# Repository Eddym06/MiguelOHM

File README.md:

# MiguelOHM

Proyecto de la materia de **Microcontroladores**: un carrito controlado a distancia, con su propio
control remoto, navegación autónoma por GPS y una página web de control desde el celular.

```
 Control remoto ──433 MHz──► ESP32-P4 ══SPI══ ESP32-S3 ──WiFi──► Celular (página web)
 (ESP32-S3 + OLED)           (cerebro del carrito)  (puerta de enlace)
```

## Qué hace

- **Control remoto** con dos joysticks, modo giroscopio, freno motor, control de luces y un OLED con
  6 pantallas (velocímetro, RPM, inclinación, estado del enlace…).
- **Carrito** con dos motores con encoder (PID de velocidad, giro por motor + servo), faros, LEDs RGB en
  las ruedas, tira LED trasera estilo F1, GPS, LIDAR, IMU y medición de batería.
- **Página web** servida por el propio carrito: control táctil, mapa con brújula, ajustes, pruebas de
  componentes y modo autónomo (el carrito va a un punto marcado en el mapa esquivando obstáculos).
- El enlace 433 MHz y el WiFi **nunca están activos a la vez**: el primero en conectarse apaga al otro.

## Estructura

| Carpeta | Contenido |
|---|---|
| [Placa_Control_Remoto/](Placa_Control_Remoto/) | PCB del control (KiCad: `KAKATA_RC433_V1`) y su firmware en [Codigo/](Placa_Control_Remoto/Codigo/README.md) (PlatformIO, Arduino, ESP32-S3). |
| [Codigo Carrito/](Codigo%20Carrito/README.md) | Firmware del carrito en ESP-IDF: `p4/` (cerebro), `s3/` (WiFi + web), `shared/` (protocolos) y `tests/`. |
| [Diseño Caja 3D/](Diseño%20Caja%203D/) | Cajas para impresión 3D (FreeCAD). |
| [Placa_Carrito/](Placa_Carrito/) | PCB del carrito (KiCad): [Tesla/](Placa_Carrito/Tesla/README.md) con un solo ESP32-S3 y expansor PCA9555, y la placa modular S3+P4. |
| [Documentación/](Documentación/) | Documento del proyecto y registro de cambios. |

## Empezar

- **Control remoto:** abrir `Placa_Control_Remoto/Codigo` con PlatformIO y `pio run -t upload`.
- **Carrito:** necesita ESP-IDF 5.5 (P4) y 5.3 o superior (S3). Instrucciones, tabla de pines pendientes y
  lista de lo que falta validar en [Codigo Carrito/README.md](Codigo%20Carrito/README.md).
- **Pruebas de la lógica del carrito en la PC:** `bash "Codigo Carrito/tests/run_host_tests.sh"`.

## Estado

| Parte | Estado |
|---|---|
| Firmware del control remoto | Compila. Pendiente de probar en la PCB. |
| Firmware del carrito (P4 y S3) | Compila; lógica pura probada en la PC (97 verificaciones). Pines pendientes de la PCB del carrito. |
| Página web | Revisada en navegador con datos simulados. Pendiente de probar con el carrito real. |

Antes de las pruebas con hardware, revisar la sección «Sin validar en hardware» del README del carrito
(sentido de ejes y motores, encoders, PID, protocolo del LIDAR y del GPS).

## Simulación

[Modelos y resultados por placa](Simulación/README.md).

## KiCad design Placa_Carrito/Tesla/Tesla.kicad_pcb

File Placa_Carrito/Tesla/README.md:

# Placa Tesla (carrito): guía del diseño

PCB del carrito con **un solo ESP32-S3** (módulo WROOM-1 N16R2) y un expansor de pines **PCA9555**. Este documento explica cómo está organizado el esquemático, qué cambió respecto a las versiones anteriores y, sobre todo, **qué implica para el código** (para Eddy).

Archivos relacionados:

| Archivo | Contenido |
|---|---|
| [ASIGNACION_PINES.md](ASIGNACION_PINES.md) | Qué va en cada GPIO del S3, en cada pin del PCA9555 y en el conector J20. |
| [CAMBIOS.md](CAMBIOS.md) | Registro detallado de los cambios de esta revisión (qué, por qué y cómo verificarlo). |
| [Tesla_BOM.csv](Tesla_BOM.csv) | Lista de materiales. |
| `Tesla.kicad_pro` | Proyecto de KiCad 10 (abrirlo desde aquí). |

## Estructura del esquemático

La hoja raíz (`Tesla.kicad_sch`) tiene dos cosas: los **conectores externos**, cada uno en su cuadro y unido con cable directo (sin etiquetas) a los pines de la hoja `Externo`, y la hoja `USB-C`. Todo lo demás vive dentro de `Externo`, donde las hojas se unen por etiquetas. Los pines de `Externo` se llaman como la señal (`SERVO_1`, `ENC_A1`, `NRF_CE`...) y por dentro se unen a la red `GPIOn` o `EXP_GPIOn` del bloque de control.

**En la raíz (lo que el usuario toca):**

| Cuadro | Conectores |
|---|---|
| Batería | J6 (borne WAGO 2604-1102, 12 V) |
| Motores | J4 y J5, un conector PH2.0 de 6 pines por motor JGB37-520 (motor y encoder juntos) |
| GPS e IMU | J10 (GPS M100 Pro) y J15 (GY-521) |
| Servos | J7 (dirección), J8 y J9 |
| LiDAR | J11 y R24 (pull-down de la señal de control) |
| Tira LED | J16 (WS2812) |
| Radio nRF24L01+ | U2 (módulo nRF24L01 con conector, fuera de la placa principal) |
| Luces | J21 y J24 (faros, uno por LED), J22 y J23 (intermitentes izquierdo y derecho): un conector PH2.0 de 2 pines por canal para los LED de 1 W |
| Expansión | J20 (socket hembra 1x16) |
| USB-C | hoja `usb.kicad_sch`: J3, protección ESD U13 y R61 y R62 (CC) |

**Dentro de `Externo`:**

| Hoja | Archivo | Contenido |
|---|---|---|
| Alimentacion | `alimentacion.kicad_sch` | Contenedor de: protección de batería (`alim_proteccion`), medición (`alim_medicion`) y dos bucks (`alim_buck_3v3` y `alim_buck_5v`; el de 5 V incluye el filtro del LiDAR). |
| Control ESP32 | `control.kicad_sch` | **Solo** el ESP32-S3 con su circuito mínimo (reset, BOOT, filtrado de 3V3) y el PCA9555 con su filtrado. Incluye los pull-ups que exige el PCA9555 en SCL, SDA e INT (4,7 kΩ, 4,7 kΩ y 10 kΩ). Los pull-downs de las salidas no van aquí: viven junto a la carga que protegen. |
| Drivers motores | `motores.kicad_sch` | DRV8424 y pull-downs de arranque de APH, BPH y nSleep. |
| Faros | `faros.kicad_sch` | Drivers del alumbrado (faros e intermitentes, AL8860; los LED van afuera) y adaptador 3,3 V a 5 V para la tira WS2812B (J16). |

Reglas de dibujo aplicadas a todas las hojas:

- En la raíz, cada señal va con cable directo del pin de `Externo` al pin del conector. Entre ICs y hojas internas se usan etiquetas (jerárquicas en el borde de cada hoja, globales entre pines internos, locales dentro de una hoja). Los cables solo unen un pasivo con su pin.
- Cada pasivo se conecta con cable corto, componente, cable corto y símbolo de alimentación. Nada se conecta directo a un nodo.
- Las flechas de 3V3, 5V y VM apuntan hacia arriba o de lado, nunca hacia abajo, y muestran su nombre.
- Los valores de componentes verticales van girados 90° junto al cuerpo.
- Cada grupo funcional va dentro de un marco punteado con título.
- Un solo GND en todo el proyecto.
- Las librerías oficiales de Espressif no se modifican.

### Conector de los motores (JGB37-520, J4 y J5)

Orden de pines del cable de 6 hilos con PH2.0 (de las imágenes del vendedor; comprobar con el motor):

| Pin | Señal | Cable |
|---|---|---|
| 1 | M1, motor + | rojo |
| 2 | GND del encoder | negro |
| 3 | C1, fase A | amarillo |
| 4 | C2, fase B | verde |
| 5 | VCC del encoder (3V3) | azul |
| 6 | M2, motor - | blanco |

Intercambiar M1 y M2 invierte el giro. El encoder (11 PPR, 3,3 a 5 V) se alimenta a 3,3 V; nunca conectar los 12 V del motor al VCC del encoder.

## Qué cambió y por qué importa al firmware

1. **Un solo microcontrolador.** El P4 salió de esta placa (vive en `../Placa_Modular_S3_P4`). Control, WiFi y web corren en el S3. El firmware actual de `Codigo Carrito/` está pensado para P4 más S3; hay que portarlo a un único S3 (tabla de pines en [ASIGNACION_PINES.md](ASIGNACION_PINES.md)).
2. **Pines de arranque sin uso.** GPIO3, GPIO45 y GPIO46 quedan sin conectar. GPIO0 es solo el botón BOOT: no se puede usar como entrada o salida del programa.
3. **Los nombres de los pines del bloque de control son GPIO.** En el firmware sigue habiendo nombres funcionales (`PIN_ENC_L_A`, etc.); la equivalencia con el GPIO está en la tabla de `ASIGNACION_PINES.md`.
4. **Expansor PCA9555.** Las señales lentas (CE e IRQ del nRF24, dirección y sleep de los motores, fallo del driver, LEDs de estado) ya no son pines del S3: se leen y escriben por I2C (ver siguiente sección).
5. **Bus I2C compartido** (GPIO39 SCL, GPIO40 SDA, pull-ups de 4,7 kΩ): GPS, IMU, INA219 y PCA9555 (0x20). **GPIO39, GPIO40 y GPIO42 (INT) no son pines libres** y no salen de la hoja de control. Por eso el GPS, la IMU, el INA219 y los pines I2C de J20 **no tienen bus I2C hacia el S3 todavía** (decisión pendiente: ver Pendiente).
6. **Radio nRF24** por SPI en GPIO10 (CSN), GPIO11 (MOSI), GPIO12 (SCK), GPIO13 (MISO). CE e IRQ van por el expansor.
7. **USB-C del S3** (hoja `USB-C`) para programar, JTAG y consola (GPIO19 D-, GPIO20 D+). UART0 (GPIO43 TX, GPIO44 RX) va a un segundo USB-C (J2, hoja `USB-UART`) con puente CH340C y auto-reset por DTR y RTS (EN y GPIO0).
8. **Motores y encoders** salen por un solo conector de 6 pines por motor (J4 y J5), con el encoder a 3,3 V.

## Programar el expansor PCA9555

Los 16 pines `EXP_GPIO0` a `EXP_GPIO15` no son GPIO del S3: son dos puertos de 8 bits que se controlan por I2C con el chip en la dirección **0x20** (A0, A1 y A2 a GND). Un bit del puerto 0 es `EXP_GPIO0` a `7`; uno del puerto 1 es `EXP_GPIO8` a `15`.

Registros (el primer byte de cada transferencia elige el registro):

| Reg | Función |
|---|---|
| 0x00 / 0x01 | Leer puerto 0 / puerto 1 (entradas) |
| 0x02 / 0x03 | Escribir salidas del puerto 0 / 1 |
| 0x04 / 0x05 | Invertir polaridad (se deja en 0) |
| 0x06 / 0x07 | Configuración del puerto 0 / 1: **1 = entrada, 0 = salida** |

Al encender, todos los pines son entradas con un pull-up interno de unos 100 kΩ. Por eso APH, BPH, nSleep y CE tienen pull-down de 10 kΩ: el driver arranca dormido y el nRF24 con CE en bajo.

Uso de cada pin en esta placa:

| Pin | Señal | Dirección |
|---|---|---|
| `EXP_GPIO0` | NRF_CE | salida |
| `EXP_GPIO1` | NRF_IRQ | entrada |
| `EXP_GPIO2`, `3`, `4` | APH, BPH, nSleep del DRV8424 | salida |
| `EXP_GPIO5` | nFAULT del DRV8424 | entrada |
| `EXP_GPIO6`, `7` | LED_AP, LED_AN | salida, **activos en bajo** |
| `EXP_GPIO8`, `9` | LED_BP, LED_BN | salida, **activos en bajo** |
| `EXP_GPIO10` a `15` | libres, salen por J20 | a elección |

Valores iniciales recomendados (se escriben antes de configurar la dirección, para que no haya pulsos): puerto 0 salidas en `0xC0` y puerto 1 en `0x03` (todo en bajo salvo los LEDs, que en alto quedan apagados). Configuración: puerto 0 en `0x22` y puerto 1 en `0xFC`.

Ejemplo con ESP-IDF 5.x (sin compilar; sirve de guía):

```c
#include "driver/i2c_master.h"

static i2c_master_dev_handle_t pca;

static void pca_write(uint8_t reg, uint8_t val) {
    uint8_t b[2] = { reg, val };
    i2c_master_transmit(pca, b, 2, 100);
}
static uint8_t pca_read(uint8_t reg) {
    uint8_t v = 0;
    i2c_master_transmit_receive(pca, &reg, 1, &v, 1, 100);
    return v;
}

void pca_init(void) {
    i2c_master_bus_handle_t bus;
    i2c_master_bus_config_t bc = {
        .i2c_port = I2C_NUM_0, .sda_io_num = GPIO_NUM_40, .scl_io_num = GPIO_NUM_39,
        .clk_source = I2C_CLK_SRC_DEFAULT, .glitch_ignore_cnt = 7,
    };
    i2c_new_master_bus(&bc, &bus);
    i2c_device_config_t dc = { .dev_addr_length = I2C_ADDR_BIT_LEN_7,
                               .device_address = 0x20, .scl_speed_hz = 400000 };
    i2c_master_bus_add_device(bus, &dc, &pca);

    pca_write(0x02, 0xC0);   // CE/APH/BPH/nSleep en 0, LEDs apagados
    pca_write(0x03, 0x03);   // LEDs del puerto 1 apagados
    pca_write(0x06, 0x22);   // puerto 0: bits 1 (IRQ) y 5 (nFAULT) son entradas
    pca_write(0x07, 0xFC);   // puerto 1: solo los bits 0 y 1 son salidas
}
```

Para cambiar un solo pin se guarda una copia del registro de salida en una variable y se modifica solo ese bit (por ejemplo `out0 |= 1 << 4; pca_write(0x02, out0);`). Para leer el fallo del driver: `pca_read(0x00) & (1 << 5)`.

Interrupción: `INT` va a **GPIO42** y baja cuando cambia alguna entrada. Se apaga al leer los registros 0x00 y 0x01. Configurar GPIO42 como entrada con flanco de bajada y leer los dos puertos en el manejador.

Límites: cada acceso tarda unos 100 µs a 400 kHz. Sirve para CE, dirección, sleep y LEDs; **no** para PWM ni señales rápidas (AEN y BEN, los PWM de los motores, están en pines nativos del S3).

## Verificación contra los datasheets

Se contrastó el diseño con el datasheet del ESP32-S3-WROOM-1 v1.8 y el del PCA9555 de TI. Detalle en [ASIGNACION_PINES.md](ASIGNACION_PINES.md#verificación-contra-los-datasheets). Correcciones hechas: C131 de 10 a 22 µF (filtrado de 3V3 del módulo) y R54 de 100 kΩ a 10 kΩ (pull-down de CE frente al pull-up interno del PCA9555).

## Pendiente

- En KiCad: **Actualizar PCB desde esquema** con la opción de actualizar huellas. Cambiaron J4 y J5 (ahora PH2.0 de 6 pines), J13 y J14 desaparecieron, J20 pasa a socket hembra y los nombres de red cambiaron con la hoja `Externo` y la hoja `USB-C`. Hasta entonces el DRC con paridad marca conflictos de red.
- Decidir cómo llega el I2C al GPS, la IMU y el INA219 (GPIO39 y GPIO40 están ocupados por el PCA9555 y no salen de Control).
- Rutear la PCB (hoy solo tiene las huellas colocadas) y revisar las reglas del DRC de U1 (anillos y taladros de las vías internas).
- Portar el firmware a un único S3 (`Codigo Carrito/`), con el driver del PCA9555 de arriba.
- Datasheets: carpeta `Datasheets/` en la raíz del repositorio (faltan algunos conectores, el GPS y el LiDAR; ver su README).

## Alimentación en la jerarquía (entradas y salidas de rieles)

- La hoja `Alimentacion` **saca** `VM`, `+3V3`, `+5V` y `GND` (bloque "Salidas de alimentacion"; el buck de 3V3, el de 5 V, la medición y la protección reciben `GND` y `VM` por pines).
- Cada hoja consumidora **recibe** solo los rieles que usa en su bloque "Entradas de alimentacion" (etiqueta jerárquica, un cablecito con giro y el símbolo de alimentación): Control (`+3V3`, `GND`), Drivers motores y Faros (`VM`, `GND`), Tira LED (`+5V`, `GND`), LEDs RGB (`+3V3`, `+5V`, `VM`, `GND`).
- En `Externo` cada pin de riel lleva una etiqueta global del mismo nombre, así todos los `GND`, `+3V3`, `+5V` y `VM` quedan unidos en toda la jerarquía. Sigue habiendo un solo `GND`.
- Los conectores de la raíz traen sus propios símbolos de alimentación (+5V, GND, +3V3...), que también son globales.

## Placa (PCB)

La placa ya tiene contorno de 130 x 170 mm, 4 capas, clases de red, zonas de cobre, zonas prohibidas de las antenas y todas las piezas colocadas (sin rutar). El detalle de la colocación, los cálculos, los cambios de piezas por existencias en JLCPCB y lo pendiente está en [PCB_NOTAS.md](PCB_NOTAS.md). La lista de piezas con códigos LCSC, existencias y precios está en `Tesla_BOM.csv` y `Tesla_BOM_JLCPCB.csv`. Se regenera con `herramientas/pcb_build.py`.

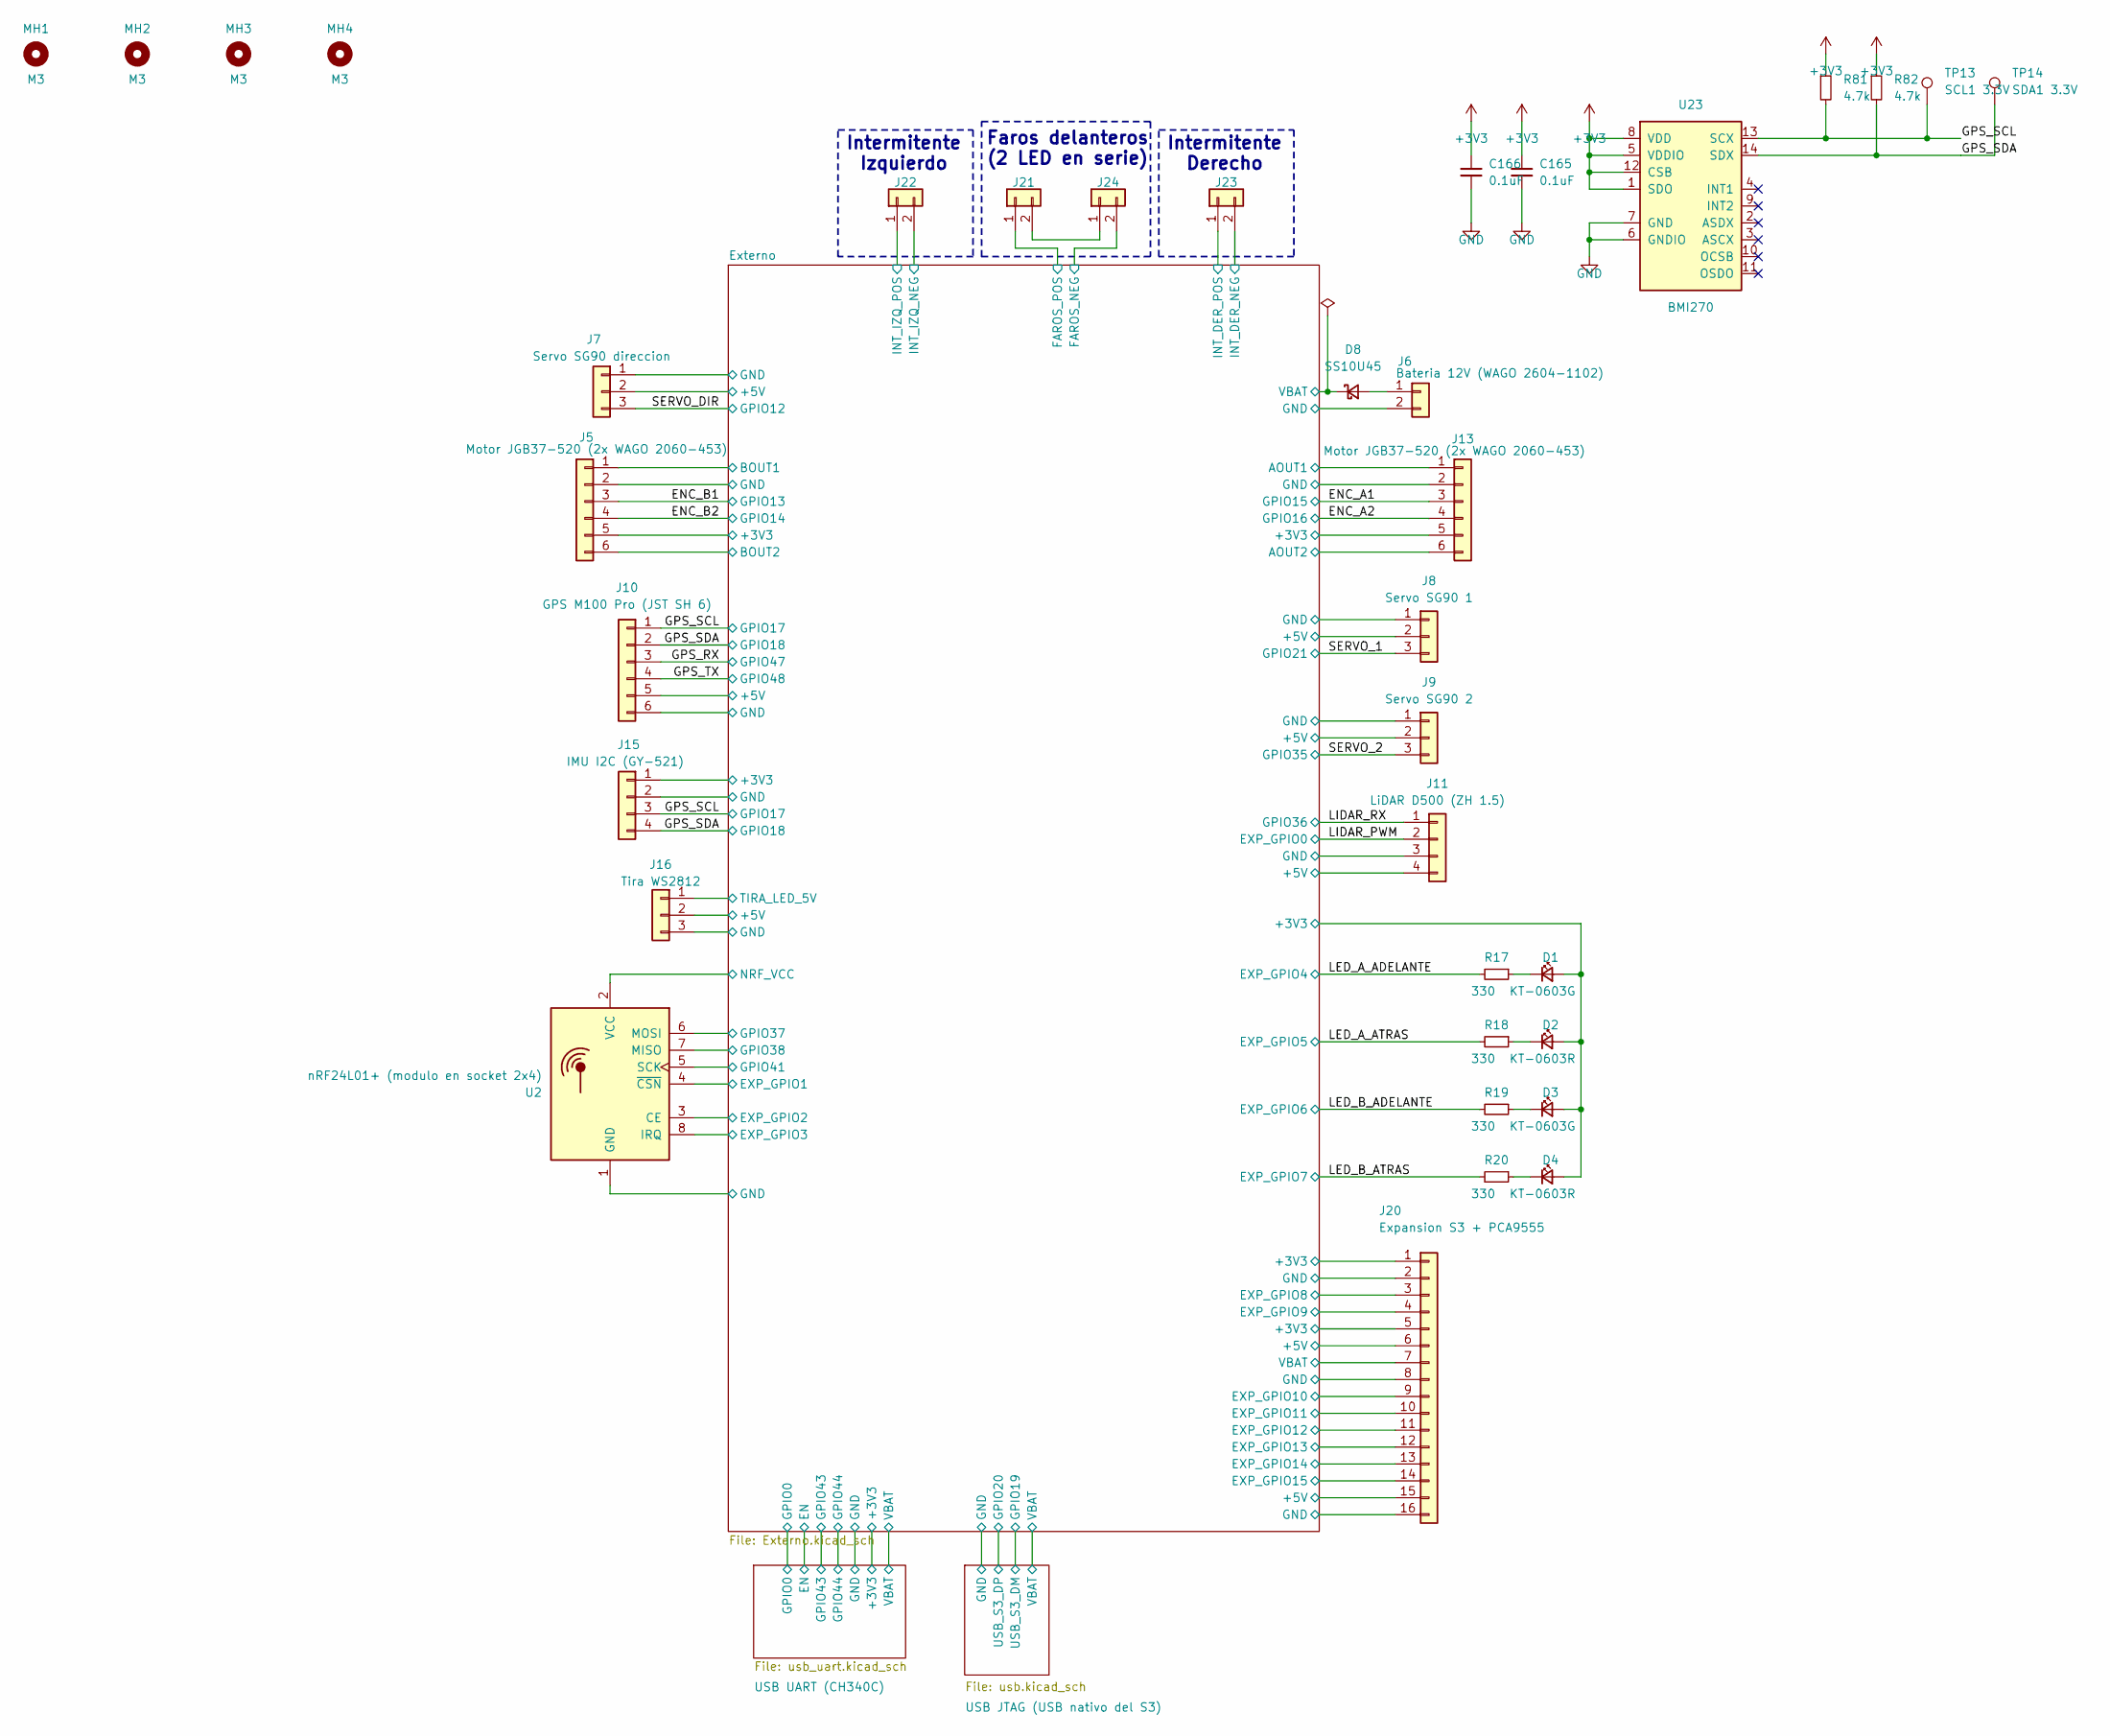
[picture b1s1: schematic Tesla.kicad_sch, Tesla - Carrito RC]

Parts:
C165, C166: 0.1uF; C_0402_1005Metric; LCSC C307331
D1, D3: KT-0603G; LED_0603_1608Metric; LCSC C12624
D2, D4: KT-0603R; LED_0603_1608Metric; LCSC C2286
D8: SS10U45; TO-277_SS10U45; LCSC C698773
J5, J13: Motor JGB37-520 (2x WAGO 2060-453); WAGO_2060-453_x2_6P_SMD; LCSC C2765056
J6: Bateria 12V (WAGO 2604-1102); WAGO_2604-1102_2P_THT; LCSC C3309286
J7: Servo SG90 direccion; PinHeader_1x03_P2.54mm_Horizontal; LCSC C492411
J8: Servo SG90 1; PinHeader_1x03_P2.54mm_Horizontal; LCSC C492411
J9: Servo SG90 2; PinHeader_1x03_P2.54mm_Horizontal; LCSC C492411
J10: GPS M100 Pro (JST SH 6); JST_SH_SM06B-SRSS-TB_1x06-1MP_P1.00mm_Horizontal; LCSC C160405
J11: LiDAR D500 (ZH 1.5); JST_ZH_B4B-ZR_1x04_P1.50mm_Vertical; LCSC C157997
J15: IMU I2C (GY-521); PinSocket_1x04_P2.54mm_Vertical; LCSC C2718488
J16: Tira WS2812; PinHeader_1x03_P2.54mm_Horizontal; LCSC C492411
J20: Expansion S3 + PCA9555; PinSocket_2x08_P2.54mm_Vertical; LCSC C30734
J21: Faro delantero 1; JST_PH_B2B-PH-K_1x02_P2.00mm_Vertical; LCSC C131337
J22: Intermitente izquierdo; JST_PH_B2B-PH-K_1x02_P2.00mm_Vertical; LCSC C131337
J23: Intermitente derecho; JST_PH_B2B-PH-K_1x02_P2.00mm_Vertical; LCSC C131337
J24: Faro delantero 2; JST_PH_B2B-PH-K_1x02_P2.00mm_Vertical; LCSC C131337
MH1, MH2, MH3, MH4: M3; MountingHole_3.2mm_M3
R17, R18, R19, R20: 330; R_0402_1005Metric; LCSC C25104
R81, R82: 4.7k; R_0402_1005Metric; LCSC C25900
TP13: SCL1 3.3V; TestPoint_Pad_D1.5mm
TP14: SDA1 3.3V; TestPoint_Pad_D1.5mm
U2: nRF24L01+ (modulo en socket 2x4); nRF24L01_Breakout; LCSC C239344
U23: BMI270; Bosch_LGA-14_3x2.5mm_P0.5mm; LCSC C2836813

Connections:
+3V3: C165.1, C166.1, D1.2 (A), D2.2 (A), D3.2 (A), D4.2 (A), J5.5, J13.5, J15.1, J20.1, J20.5, R81.1, R82.1, U2.2 (VCC), U23.1 (SDO), U23.5 (VDDIO), U23.8 (VDD), U23.12 (CSB); also elsewhere on the board
+5V: J7.2, J8.2, J9.2, J10.5, J11.4, J16.2, J20.6, J20.15; also elsewhere on the board
/ENC_A1: J13.3; also elsewhere on the board
/ENC_A2: J13.4; also elsewhere on the board
/ENC_B1: J5.3; also elsewhere on the board
/ENC_B2: J5.4; also elsewhere on the board
/Externo/AOUT1: J13.1; also elsewhere on the board
/Externo/AOUT2: J13.6; also elsewhere on the board
/Externo/BOUT1: J5.1; also elsewhere on the board
/Externo/BOUT2: J5.6; also elsewhere on the board
/Externo/EXP_GPIO1: U2.4 (~CSN); also elsewhere on the board
/Externo/EXP_GPIO2: U2.3 (CE); also elsewhere on the board
/Externo/EXP_GPIO3: U2.8 (IRQ); also elsewhere on the board
/Externo/EXP_GPIO8: J20.3; also elsewhere on the board
/Externo/EXP_GPIO9: J20.4; also elsewhere on the board
/Externo/EXP_GPIO10: J20.9; also elsewhere on the board
/Externo/EXP_GPIO11: J20.10; also elsewhere on the board
/Externo/EXP_GPIO12: J20.11; also elsewhere on the board
/Externo/EXP_GPIO13: J20.12; also elsewhere on the board
/Externo/EXP_GPIO14: J20.13; also elsewhere on the board
/Externo/EXP_GPIO15: J20.14; also elsewhere on the board
/Externo/FAROS_NEG: J24.2; also elsewhere on the board
/Externo/FAROS_POS: J21.1; also elsewhere on the board
/Externo/GPIO37: U2.6 (MOSI); also elsewhere on the board
/Externo/GPIO38: U2.7 (MISO); also elsewhere on the board
/Externo/GPIO41: U2.5 (SCK); also elsewhere on the board
/Externo/INT_DER_NEG: J23.2; also elsewhere on the board
/Externo/INT_DER_POS: J23.1; also elsewhere on the board
/Externo/INT_IZQ_NEG: J22.2; also elsewhere on the board
/Externo/INT_IZQ_POS: J22.1; also elsewhere on the board
/Externo/TIRA_LED_5V: J16.1; also elsewhere on the board
/Externo/VBAT: D8.1 (K), J20.7; also elsewhere on the board
/GPS_RX: J10.3; also elsewhere on the board
/GPS_SCL: J10.1, J15.3, R81.2, TP13.1, U23.13 (SCX); also elsewhere on the board
/GPS_SDA: J10.2, J15.4, R82.2, TP14.1, U23.14 (SDX); also elsewhere on the board
/GPS_TX: J10.4; also elsewhere on the board
/LED_A_ADELANTE: R17.2; also elsewhere on the board
/LED_A_ATRAS: R18.2; also elsewhere on the board
/LED_B_ADELANTE: R19.2; also elsewhere on the board
/LED_B_ATRAS: R20.2; also elsewhere on the board
/LIDAR_PWM: J11.2; also elsewhere on the board
/LIDAR_RX: J11.1; also elsewhere on the board
/SERVO_1: J8.3; also elsewhere on the board
/SERVO_2: J9.3; also elsewhere on the board
/SERVO_DIR: J7.3; also elsewhere on the board
GND: C165.2, C166.2, J5.2, J6.2, J7.1, J8.1, J9.1, J10.6, J11.3, J13.2, J15.2, J16.3, J20.2, J20.8, J20.16, U2.1 (GND), U23.6 (GNDIO), U23.7 (GND); also elsewhere on the board
unnamed: D1.1 (K), R17.1
unnamed: D2.1 (K), R18.1
unnamed: D3.1 (K), R19.1
unnamed: D4.1 (K), R20.1
unnamed: D8.2 (A), J6.1
unnamed: J21.2, J24.1

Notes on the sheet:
Intermitente Derecho
Faros delanteros (2 LED en serie)
Intermitente Izquierdo

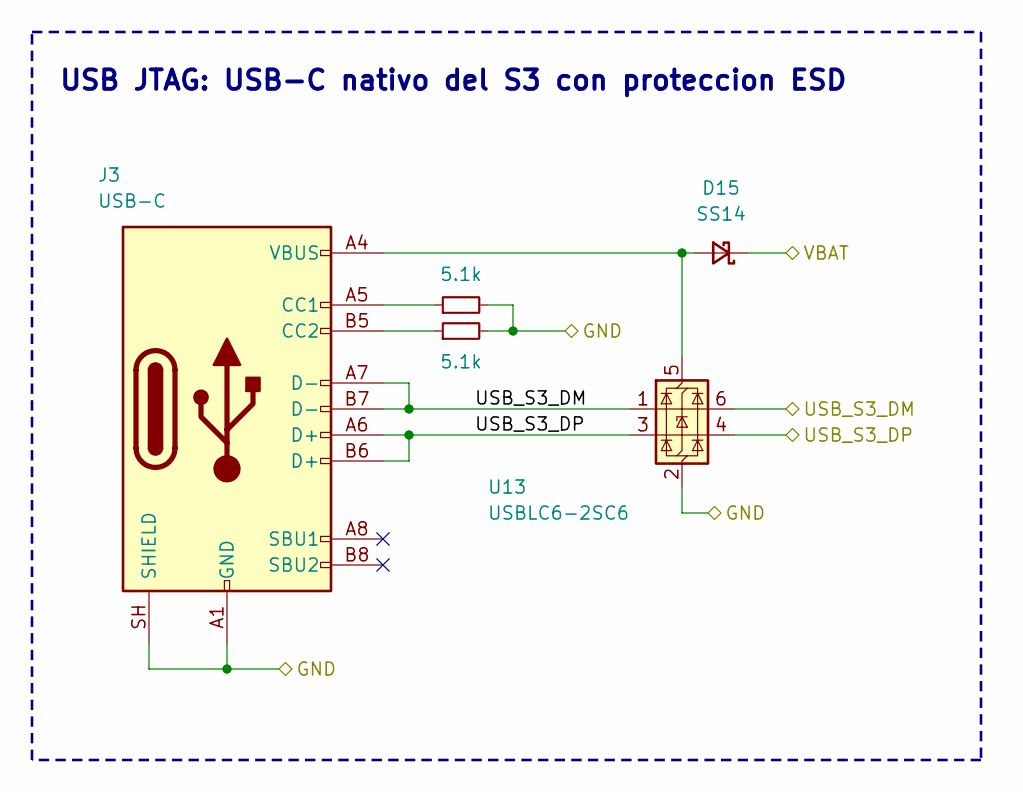
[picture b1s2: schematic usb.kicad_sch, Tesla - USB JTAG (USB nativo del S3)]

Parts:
D15: SS14; D_SMA; LCSC C2480
J3: USB-C; USB_C_Receptacle_HRO_TYPE-C-31-M-12; LCSC C165948
R61, R62: 5.1k; R_0402_1005Metric; LCSC C25905
U13: USBLC6-2SC6; SOT-23-6; LCSC C7519

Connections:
/Externo/VBAT: D15.1 (K); also elsewhere on the board
/USB JTAG (USB nativo del S3)/USB_S3_DM: J3.A7 (D-), J3.B7 (D-), U13.1 (I/O1), U13.6 (I/O1); also elsewhere on the board
/USB JTAG (USB nativo del S3)/USB_S3_DP: J3.A6 (D+), J3.B6 (D+), U13.3 (I/O2), U13.4 (I/O2); also elsewhere on the board
GND: J3.A1 (GND), J3.A12 (GND), J3.B1 (GND), J3.B12 (GND), J3.SH (SHIELD), R61.2, R62.2, U13.2 (GND); also elsewhere on the board
unnamed: D15.2 (A), J3.A4 (VBUS), J3.A9 (VBUS), J3.B4 (VBUS), J3.B9 (VBUS), U13.5 (VBUS)
unnamed: J3.A5 (CC1), R61.1
unnamed: J3.B5 (CC2), R62.1

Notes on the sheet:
USB JTAG: USB-C nativo del S3 con proteccion ESD

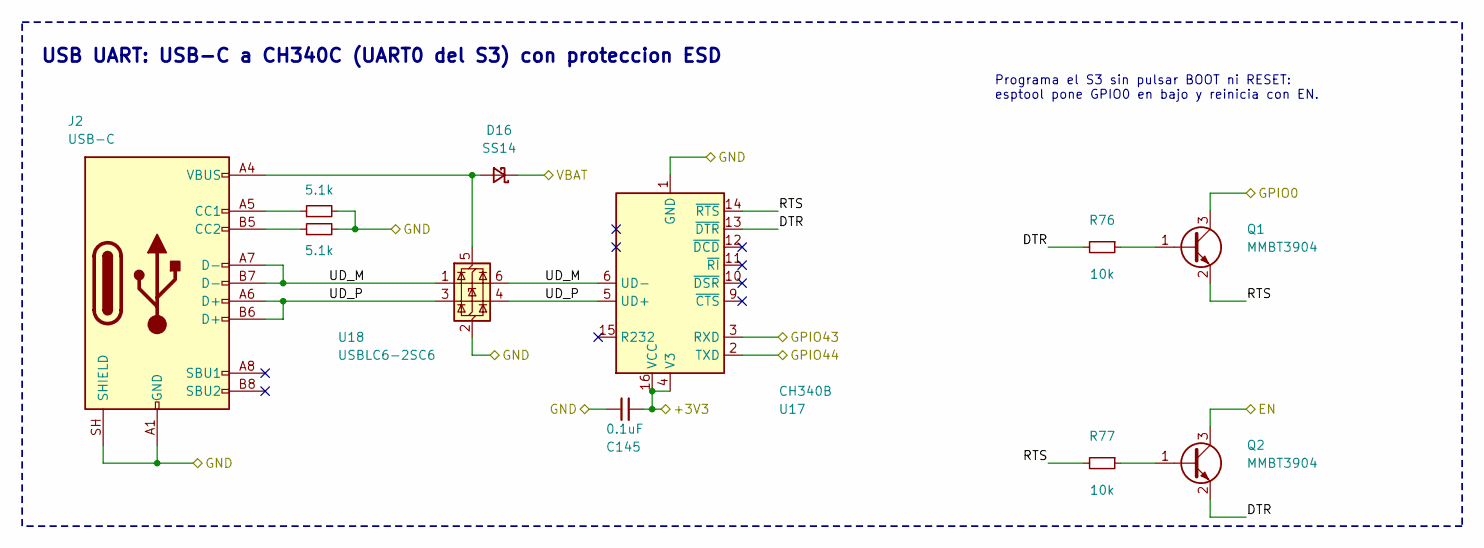
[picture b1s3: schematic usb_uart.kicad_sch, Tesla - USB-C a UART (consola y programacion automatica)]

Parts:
C145: 0.1uF; C_0402_1005Metric; LCSC C307331
D16: SS14; D_SMA; LCSC C2480
J2: USB-C; USB_C_Receptacle_HRO_TYPE-C-31-M-12; LCSC C165948
Q1, Q2: MMBT3904; SOT-23; LCSC C20526
R74, R75: 5.1k; R_0402_1005Metric; LCSC C25905
R76, R77: 10k; R_0402_1005Metric; LCSC C25744
U17: CH340B; SOIC-16_3.9x9.9mm_P1.27mm; LCSC C81010
U18: USBLC6-2SC6; SOT-23-6; LCSC C7519

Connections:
+3V3: C145.1, U17.4 (V3), U17.16 (VCC); also elsewhere on the board
/Externo/EN: Q2.3 (C); also elsewhere on the board
/Externo/GPIO0: Q1.3 (C); also elsewhere on the board
/Externo/GPIO43: U17.3 (RXD); also elsewhere on the board
/Externo/GPIO44: U17.2 (TXD); also elsewhere on the board
/Externo/VBAT: D16.1 (K); also elsewhere on the board
/USB UART (CH340C)/DTR: Q2.2 (E), R76.2, U17.13 (~DTR)
/USB UART (CH340C)/RTS: Q1.2 (E), R77.2, U17.14 (~RTS)
/USB UART (CH340C)/UD_M: J2.A7 (D-), J2.B7 (D-), U17.6 (UD-), U18.1 (I/O1), U18.6 (I/O1)
/USB UART (CH340C)/UD_P: J2.A6 (D+), J2.B6 (D+), U17.5 (UD+), U18.3 (I/O2), U18.4 (I/O2)
GND: C145.2, J2.A1 (GND), J2.A12 (GND), J2.B1 (GND), J2.B12 (GND), J2.SH (SHIELD), R74.2, R75.2, U17.1 (GND), U18.2 (GND); also elsewhere on the board
unnamed: D16.2 (A), J2.A4 (VBUS), J2.A9 (VBUS), J2.B4 (VBUS), J2.B9 (VBUS), U18.5 (VBUS)
unnamed: J2.A5 (CC1), R74.1
unnamed: J2.B5 (CC2), R75.1
unnamed: Q1.1 (B), R76.1
unnamed: Q2.1 (B), R77.1

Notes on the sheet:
USB UART: USB-C a CH340C (UART0 del S3) con proteccion ESD
Programa el S3 sin pulsar BOOT ni RESET: esptool pone GPIO0 en bajo y reinicia con EN.

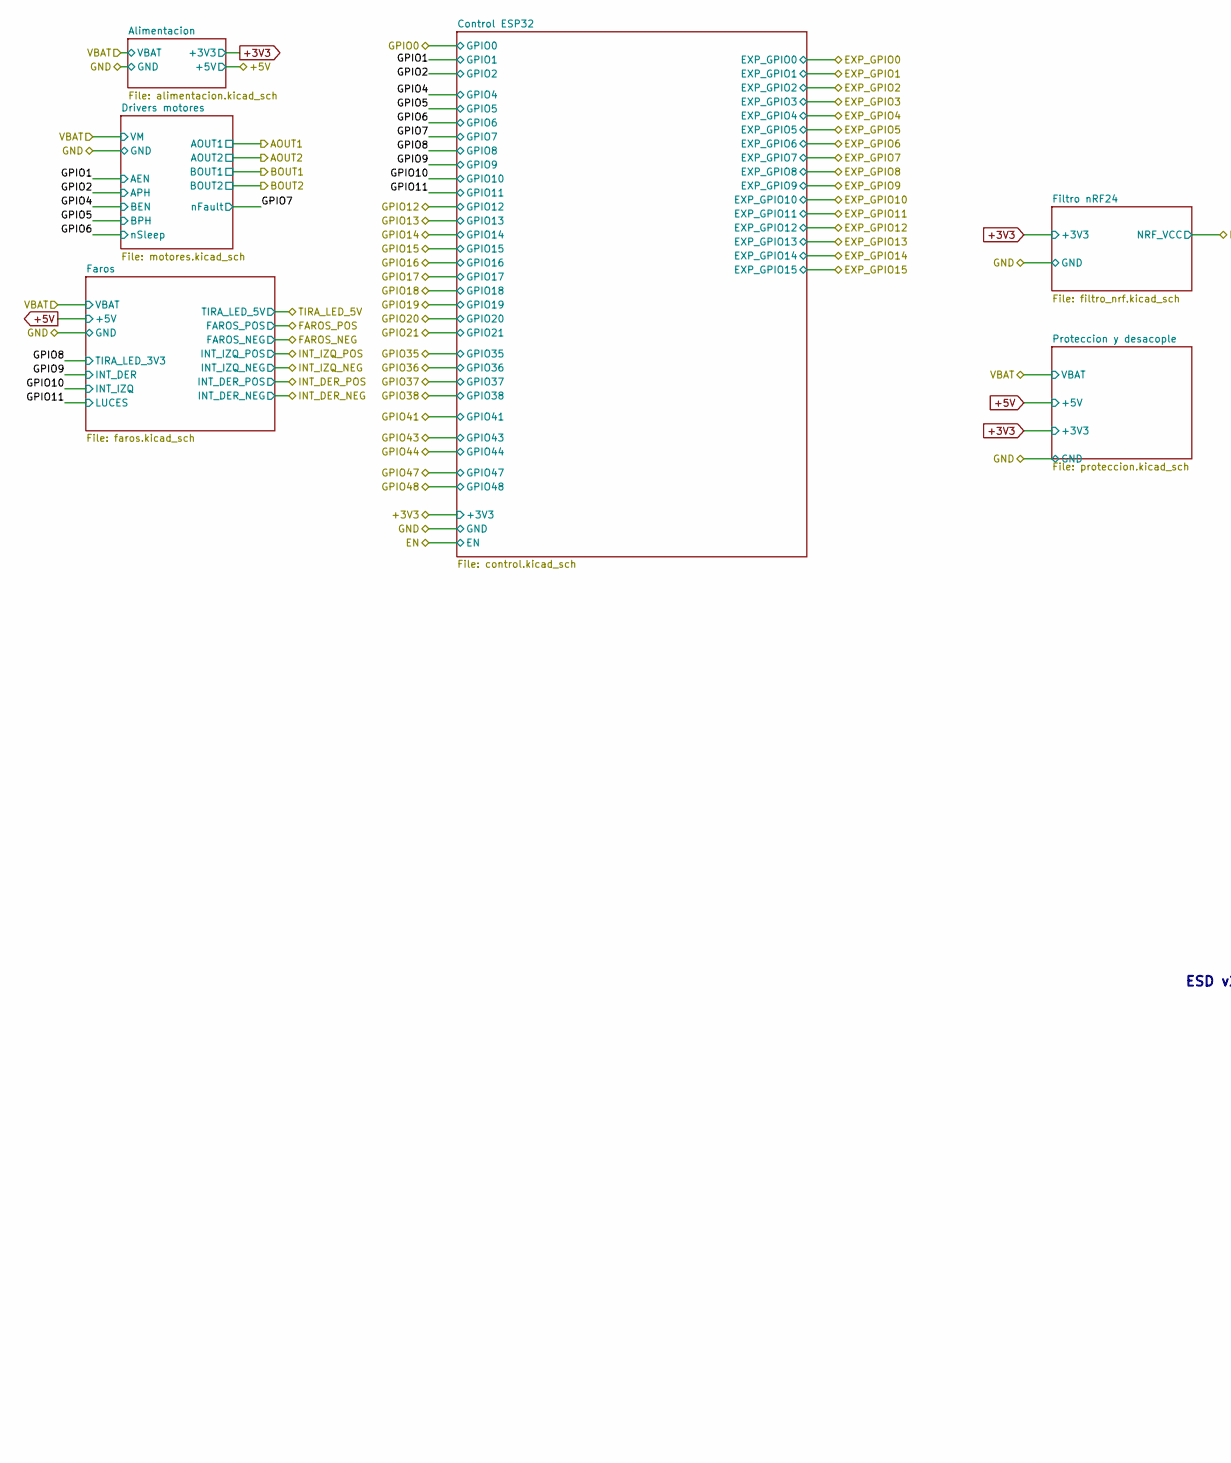
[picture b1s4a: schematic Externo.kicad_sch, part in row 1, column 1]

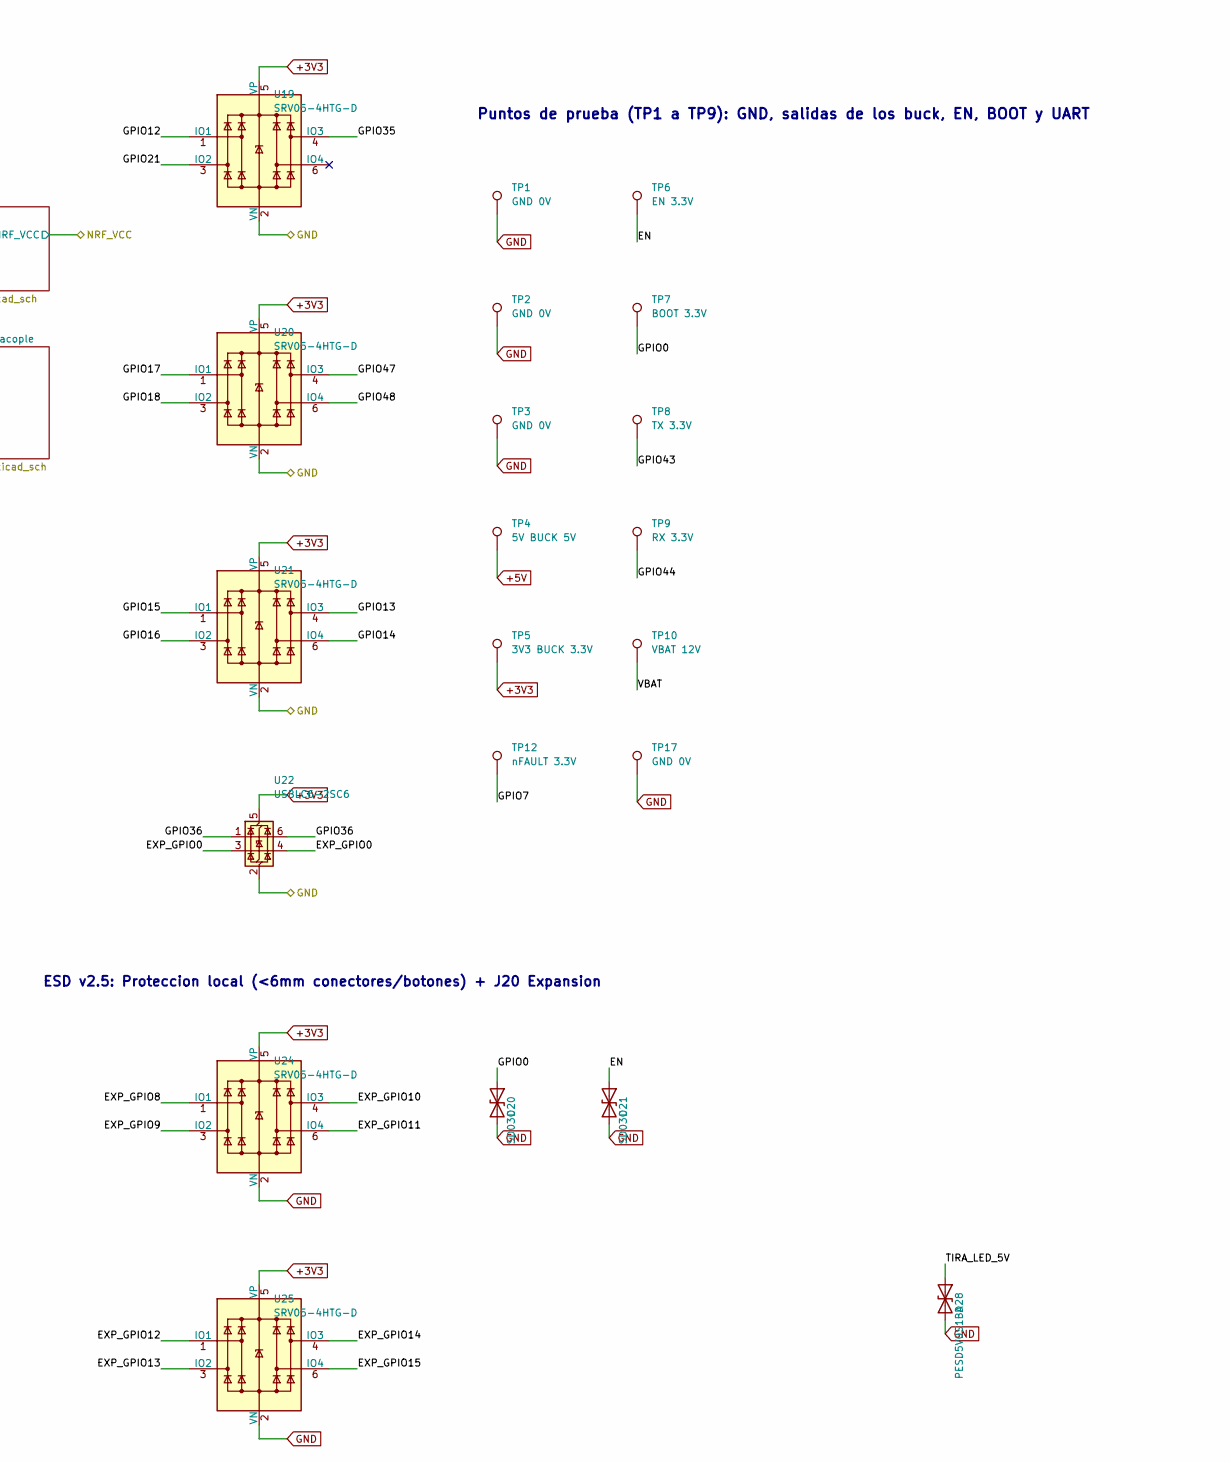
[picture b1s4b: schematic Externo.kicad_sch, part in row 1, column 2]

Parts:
D20, D21: SD03C; D_SOD-323; LCSC C502532
D28: PESD5V0S1BA; D_SOD-323; LCSC C2827694
TP1, TP2, TP3, TP17: GND 0V; TestPoint_Pad_D1.5mm
TP4: 5V BUCK 5V; TestPoint_Pad_D1.5mm
TP5: 3V3 BUCK 3.3V; TestPoint_Pad_D1.5mm
TP6: EN 3.3V; TestPoint_Pad_D1.5mm
TP7: BOOT 3.3V; TestPoint_Pad_D1.5mm
TP8: TX 3.3V; TestPoint_Pad_D1.5mm
TP9: RX 3.3V; TestPoint_Pad_D1.5mm
TP10: VBAT 12V; TestPoint_Pad_D1.5mm
TP12: nFAULT 3.3V; TestPoint_Pad_D1.5mm
U19, U20, U21, U24, U25: SRV05-4HTG-D; SOT-23-6; LCSC C1975211
U22: USBLC6-2SC6; SOT-23-6; LCSC C7519

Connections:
+3V3: TP5.1, U19.5 (VP), U20.5 (VP), U21.5 (VP), U22.5 (VBUS), U24.5 (VP), U25.5 (VP); also elsewhere on the board
+5V: TP4.1; also elsewhere on the board
/ENC_A1: U21.1 (IO1); also elsewhere on the board
/ENC_A2: U21.3 (IO2); also elsewhere on the board
/ENC_B1: U21.4 (IO3); also elsewhere on the board
/ENC_B2: U21.6 (IO4); also elsewhere on the board
/Externo/EN: D21.1 (A1), TP6.1; also elsewhere on the board
/Externo/EXP_GPIO8: U24.1 (IO1); also elsewhere on the board
/Externo/EXP_GPIO9: U24.3 (IO2); also elsewhere on the board
/Externo/EXP_GPIO10: U24.4 (IO3); also elsewhere on the board
/Externo/EXP_GPIO11: U24.6 (IO4); also elsewhere on the board
/Externo/EXP_GPIO12: U25.1 (IO1); also elsewhere on the board
/Externo/EXP_GPIO13: U25.3 (IO2); also elsewhere on the board
/Externo/EXP_GPIO14: U25.4 (IO3); also elsewhere on the board
/Externo/EXP_GPIO15: U25.6 (IO4); also elsewhere on the board
/Externo/GPIO0: D20.1 (A1), TP7.1; also elsewhere on the board
/Externo/GPIO7: TP12.1; also elsewhere on the board
/Externo/GPIO43: TP8.1; also elsewhere on the board
/Externo/GPIO44: TP9.1; also elsewhere on the board
/Externo/TIRA_LED_5V: D28.1 (A1); also elsewhere on the board
/Externo/VBAT: TP10.1; also elsewhere on the board
/GPS_RX: U20.4 (IO3); also elsewhere on the board
/GPS_SCL: U20.1 (IO1); also elsewhere on the board
/GPS_SDA: U20.3 (IO2); also elsewhere on the board
/GPS_TX: U20.6 (IO4); also elsewhere on the board
/LIDAR_PWM: U22.3 (I/O2), U22.4 (I/O2); also elsewhere on the board
/LIDAR_RX: U22.1 (I/O1), U22.6 (I/O1); also elsewhere on the board
/SERVO_1: U19.3 (IO2); also elsewhere on the board
/SERVO_2: U19.4 (IO3); also elsewhere on the board
/SERVO_DIR: U19.1 (IO1); also elsewhere on the board
GND: D20.2 (A2), D21.2 (A2), D28.2 (A2), TP1.1, TP2.1, TP3.1, TP17.1, U19.2 (VN), U20.2 (VN), U21.2 (VN), U22.2 (GND), U24.2 (VN), U25.2 (VN); also elsewhere on the board

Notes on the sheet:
Puntos de prueba (TP1 a TP9): GND, salidas de los buck, EN, BOOT y UART
ESD v2.5: Proteccion local (<6mm conectores/botones) + J20 Expansion

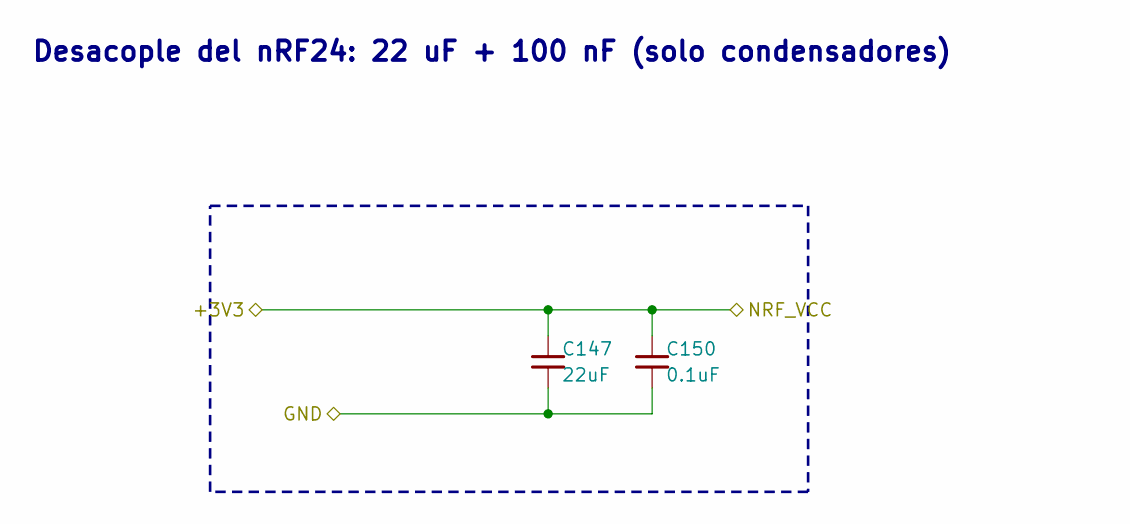
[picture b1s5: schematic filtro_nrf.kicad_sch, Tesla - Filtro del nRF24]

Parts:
C147: 22uF; C_0805_2012Metric; LCSC C45783
C150: 0.1uF; C_0402_1005Metric; LCSC C307331

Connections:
+3V3: C147.1, C150.1; also elsewhere on the board
GND: C147.2, C150.2; also elsewhere on the board

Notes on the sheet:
Desacople del nRF24: 22 uF + 100 nF (solo condensadores)
